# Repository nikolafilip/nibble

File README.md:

# Nibble

A 4-bit computer built from individual transistors, in public.

No integrated circuits anywhere. Transistors, resistors, diodes, capacitors,
LEDs, switches, connectors and wire. Every board is designed in KiCad,
simulated in ngspice, fabricated as a through-hole PCB and hand-soldered.

An AI (Claude) does the schematic generation, simulation and layout.
Nikola sets the constraints, reviews, orders, solders and measures.
The commit trailers say which is which.

## Layout

| Path | What |
|---|---|
| `docs/` | Architecture, instruction set, bus header, gate cell, build plan, decision ledger, known issues |
| `boards/00-origin-calculator/` | The hand-made 3-bit add/subtract calculator this started from, untouched |
| `boards/01-alu/` | 4-bit ALU: add, subtract, and, or, xor, increment, decrement, with flags |
| `boards/02-registers/` | A, B and OUT registers |
| `boards/03-sequencer/` | Step counter, instruction and operand registers, flags, decoders and the diode control matrix |
| `boards/04-program/` | Program memory: 16 words on DIP switches, one page of 256; build more for longer programs |
| `boards/05-clock/` | Clock with a speed knob, RUN/STEP, halt and power-on reset |
| `boards/06-panel/` | Front panel: switches for every line, LEDs on every line, the input port |
| `boards/07-hub/` | Bus hub: power, pull-ups, eight slots |
| `boards/08-memory/` | Data memory: 16 slots of 4 bits, every cell with an LED |
| `boards/09-counter/` | 8-bit program counter and return register |
| `coupon/` | Gate-cell test board: measure the real cell before trusting anything |
| `lib/` | Shared SPICE models and KiCad libraries |
| `sim/` | Generators, testbenches, the emulator and the whole-machine simulation |
| `experiments/muldiv/` | A multiplier/divider designed on the original RTL calculator. Simulated, not built |

## Start here

1. `docs/architecture.md` — what the machine is and how the boards fit together.
2. `docs/isa.md` — the instruction set (31 instructions in 16 opcodes) and a worked program.
3. `docs/bus-header.md` — the 64-pin ribbon header every board shares.
4. `docs/gate-cell.md` — the one logic cell everything is made of.
5. `docs/plan.md` — the gates every board passes before copper exists, and the whole-machine simulation.
6. `docs/cards.md` — the machine as 100 x 100 mm cards on one crimped ribbon (2026-09-10 evening), and the order of work from here.
7. `docs/mounting.md` — the panel it stands on.
8. `docs/DECISIONS.md` — why things are the way they are, in order.

## Status

See `docs/DECISIONS.md` for the latest entry and `docs/KNOWN-ISSUES.md` for what is wrong.

## Licence

CERN-OHL-P-2.0 for the hardware, MIT-equivalent terms for the scripts. See `LICENSE`.

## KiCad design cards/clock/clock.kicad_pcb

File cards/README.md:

# Cards

The machine as 100 x 100 mm boards on one crimped ribbon (docs/cards.md, D042
to D045). Every card has the 64-pin bus header along its top edge, soldered on the
back (D059; pin 1 top left as the front sees the holes, `docs/bus-header.md`),
two M3 holes mid-height on the sides, 100 nF + 10 uF at the top
right, and its logic on the dense tile: 7.68 mm columns, one TO-92 per 5.08
mm row, the pull-up lying along the row above its stack, GND and +5V rails
alternating between the columns on the back. Generated by `sim/build_*_card.py`
from the gate lists in `sim/`; laid out and routed by `sim/pcb.py`. Do not
hand-edit the schematics. Each card's `fab/` folder has the gerbers and their
zip, two renders, the assembly drawing (`<card>-assembly.svg`: which value
goes where, the boards print none) and the parts list. The Nibble logo
(`lib/logo/nibble.png` traced by `sim/logo.py`) is on the sequencer's
front silkscreen alone, one maker's mark on the machine; the cards carry
their name.

| Card | Directory | Transistors | Bus signals | Neighbour link |
|---|---|---|---|---|
| Register bit 0..3 | `reg0` .. `reg3` | 99 each | in: BUS<i>#, CLK, AI, AO, BI, BO, BA, AB, OI. out: A<i>, B<i>. BUS<i># driven open-drain when AO or BO | none |
| ALU bit 0..3 | `alu0` .. `alu3` | 66, 68, 68, 73 | in: A<i>, B<i>, SUB, ONE, F1, F0, EO. out: BUS<i># (open drain); bit 3 also CF, ZF | 2x3: carry C<i+1> and zero-so-far ZS<i> to bit i+1 |
| Counter bit 0..7 | `ctr0` .. `ctr7` | 62 (59 for bit 7) | in: PCL, CLK, RST (bit 0 also PCE). out: PC<i> | 2x3: count carry TC<i+1> to bit i+1; 2x6 chained ribbon from the sequencer: OPR<i>, PCR, RAI |
| Memory control | `memctl` | 57 | in: BUS3..0#, MAI, MI, MO, CLK | 2x6 chained ribbon to the slot cards: MAR3..0 and complements, MIN, MON |
| Memory slot pair | `memslot` (x8) | 91 | BUS3..0# in (MI) and out (MO, open drain) | the ribbon from memory control; jumpers A3 A2 A1 pick the pair |
| Program, four words | `prog` (one per four words) | 41 + 32 diodes | in: PC7..0. out: M7..0 through diodes | none; jumpers P7 P6 P5 P4 G3 G2 pick the addresses 4c..4c+3 |
| Clock | `clock` | 15 + the Schmitt pair | in: HLT. out: CLK, RST | none |
| Hub | `hub` | 0 | every line, on two headers | none |
| Panel A, B, C | `panela`, `panelb`, `panelc` | 28, 20, 32 | A: A3..B0, SUB..AB switched and shown, D3..0 CF ZF CLK RST shown. B: OI..MAI, MI..INP switched and shown, CLK and RST buttons. C: PC7..0, M7..0 shown, DATA switches driven onto BUS# while INP | none |
| Coupon | `coupon` | 57 | power only (a 2-pin header for the bench supply) | none |

## Register bit cards (`reg0` .. `reg3`)

Bit i of the three registers on the bus: A and B (the ALU's operands) and
OUT (the display), as three master-slave D flip-flops with their input muxes
(A takes the bus when AI, B when AB, else holds; B takes the bus when BI, A
when BA, else holds; OUT takes the bus when OI, else holds), the bus driver,
and the card's own two-phase clock (PH1, PH2 from CLK, D033) and hold
decoders. Four designs, the bit baked in, because a bit is three bus lines
and two cards jumpered alike would fight over them. `sim/registers.build_bit`
is the same logic as board 02 sliced per bit; the boards' testbench and the
machine deck take the four cards as the group `regc`.

Verification (2026-09-10), from the kicad-cli exports of the four routed cards
on one bus (`sim/tb_registers.py cards`), the 113-step register script: every
value through A and B, A and B driven back, MOV, XCH, OUT, holds:

| Netlist | Corner | Result |
|---|---|---|
| kicad-cli exports, four cards | TYP, LO, HI | 113 / 113 each |
| kicad-cli exports, four cards | MIX seeds 1, 2, 3 | 113 / 113 each |
| gate list (`cards@dev`) | TYP, LO, HI, MIX 1, 2, 3 | 113 / 113 each |

Machine gate (2026-09-11): `sim/gate.py --boards alu,hub,regc`, all twelve
programs at TYP with the four cards in the deck, 0 mismatches each (fib 127
ticks, calc 616, lfsr 1497, sort 974, mul 314, the rest between).

Layout: each card routes DRC-clean in one freerouting pass (0 unconnected),
ERC clean, 10.3 of 11 tile columns used.

Reproduce from `sim/`:

```
python3 build_reg_card.py 0                    # and 1, 2, 3
<kicad python> pcb.py ../cards/reg0 reg0
python3 tb_registers.py cards out/tb_regcards --corner MIX --seed 2
python3 machine.py programs/fib.asm --boards alu,hub,regc --corner TYP
```

## ALU bit cards (`alu0` .. `alu3`)

Bit i of the ALU: the full adder/subtractor bit (B xor SUB, carry in from
bit i-1), AND, OR, XOR selected by F1 F0, and the open-drain bus driver
while EO. Bit 0 starts the carry with SUB and the zero chain; bit 3 ends
them in CF and ZF on the bus. The carry and zero-so-far run over a 2x3 IDC
link between neighbouring cards (`frame.card_links`: IN at the bottom left,
OUT at the bottom right). `sim/alu.build_bit` is board 01 sliced per bit;
the group `aluc` stands for the four cards in the machine deck.

Verification, from the kicad-cli exports of the four routed cards chained by
their links (`sim/tb_alu.py cards --cases exhaustive`): every A, B, SUB, ONE,
F1 F0 combination, 2304 cases.

| Netlist | Corner | Result |
|---|---|---|
| kicad-cli exports, four cards | TYP | 2304 / 2304, worst settle 54 us |
| kicad-cli exports, four cards | LO | 2304 / 2304, worst settle 28 us |
| kicad-cli exports, four cards | HI | 2304 / 2304, worst settle 90 us |
| kicad-cli exports, four cards | MIX seed 1 | 2304 / 2304, worst settle 69 us |
| gate list (`cards@dev`) | TYP | 2304 / 2304 |

Layout: alu0 and alu3 route in one freerouting pass; alu1 and alu2 needed
the 300-pass cap and the 0.6 mm via (their last net drops from the bus
header into the first column). All four DRC clean, 0 unconnected.

## Counter bit cards (`ctr0` .. `ctr7`)

Bit i of the program counter (count when PCE, load the jump target OPR<i>
when PCL, load the return address RA<i> when PCR, clear on RST) and of the
return register RA (a transparent latch open while RAI and PH1). The count
carry TC<i+1> = TC<i> and PC<i> runs over the 2x3 links; the sequencer's
operand and load lines come down a chained 2x6 ribbon (`frame.card_ribbon`),
each card taking its own OPR line. Group `ctrc`.

Verification: `call.asm` on the eight cards from the gate lists, 0
mismatches; the exports carry every program of the step 9 gate
(`sim/results/gate25_*.md`).

## Memory control and slot cards (`memctl`, `memslot`)

Control: the four-bit address register MAR (transparent latches open while
MAI and MPH) and the write and read gates MIN (low while MI and MPH) and
MON (low while MO), sent to the slot cards over a chained 2x6 ribbon with
MAR and its complements. MPH is a pulse in the middle of the tick (D054):
CLKD is CLK through 100k into 2.2 nF on the sheet, and MPH = NOR(CLK, NOT
CLKD) is high from the falling edge of CLK until CLKD decays past a
threshold, 60 to 350 us, so the address latch closes and the write ends
hundreds of microseconds before the next rising edge. The first card gated
both with PH1, the low half of CLK, which ends at the rising edge: with the
clock card's 35 us edge and the threshold spread between cards, the
sequencer stepped and the next tick's data reached the bus 10 us before this
card saw the edge, and the address latch took the data as the address (gcd,
list and logic at mixed seed 2 wrote slots 12, 9 and 15 instead of 0). Slot pair:
two 4-bit slots (even: MAR0 = 0, odd: MAR0 = 1) of the pair the three
jumpers select (A3 A2 A1: the centre pin to '1' where the address bit is 1),
eight cross-coupled cells with their write and read pull-downs, and an LED
per cell. One design, eight cards, jumpered 0 to 7. Group `memc`.

The jumpers bring MAR1..3 (or their complements) onto the card, so in the
deck they are ports of the slot subcircuit (`machine.ports_of`); left
inside they float, and every read came from slot pair 7.

Verification, `sim/tb_memory.py cards`: three fills of all sixteen slots
and reads back, single writes between reads, bus noise while nothing loads,
217 steps. `--race` is the edge as the memory card saw it in the machine:
CLK rises over 35 us, the bus switches 10 us into the rise and the control
lines 100 us after it (they lag every edge by 60 to 170 us).

| Netlist | Corner | Result |
|---|---|---|
| PH1-gated card (before D054), gate list, `--race` | TYP, HI, MIX 1, MIX 2 | 121, 121, 121, 170 / 217 (`sim/out/tb_memory_oldD054_race.log`) |
| PH1-gated card (before D054), gate list, `--race` | LO | 217 / 217 (the card sees the edge at 0.8 V, before the bus moves) |
| D054 card, gate list (`dev`) | TYP, LO, HI, MIX 1..4 | 217 / 217 each (`sim/out/tbmem54_dev.log`, `tbmem54_mix.log`) |
| D054 card, gate list (`dev`), `--race` | TYP, LO, HI, MIX 1..4 | 217 / 217 each |
| D054 card, kicad-cli exports, control + eight slot cards | TYP; `--race` TYP, LO, HI, MIX 1, MIX 2 | 217 / 217 each (`sim/out/tbmem54_cards.log`) |

Layout: both cards route DRC clean in one pass, 0 unconnected.

## Program card (`prog`)

Four words of eight DIP switches; a closed switch pulls its M line high
through a diode while the word's row is selected (3.3k row pull-ups, so a
row of eight ones still reads 3.8 V against the hub's 220k, D048). Six 1x3 jumpers strap the
card to its addresses: P7..P4 the page (PC7..4), G3 G2 the word group
(PC3..2), the centre pin to '1' where the address bit is 1; PC1..0 pick the
word. A program of n words takes ceil(n/4) cards (`list` 6, `sort` 20). In
the deck (`progc`) one copy per four words is instantiated with its jumpers
and switches set from the assembled program; `prog.map.json` says which
diode is word w bit i.

Verification: `fib.asm` on the card gate lists with the ALU and hub, 0
mismatches; the exports carry every program of the step 9 gate
(`sim/results/gate25_*.md`).

## Clock card (`clock`)

Board 05's circuit on a card: the source-coupled Schmitt RC oscillator with
the speed pot and SLOW jumper, the RUN/STEP switch, the halt gate, the
power-on reset, and the hold-off (`sim/clock.py`, drawn by
`build_clock_card.py`). The hold-off (D064): a 2N7000 from the oscillator's
timing node X to ground through 100 ohm, its gate on the RST line. While
RST is high the timing capacitor is held empty, the Schmitt trigger reads
low and the clock gate holds CLK low; when RST lets go, the card's own
reset or the panel's button, X charges from 0 V and the first clock edge
comes 1.3 to 5.7 ms later at the fastest setting (`sim/results/reset_release.md`,
`starts_hold.md`), never in the 45 us in which the cards leave their
resets, which had started the machine wrong once in a hundred times
(`sweep_por.md`). HLT
reaches the halt gate through 100k into 2.2 nF (0.22 ms, D050), so the
clock pulse that started the halt step completes before the clock stops.
CLK's pull-up in RUN is 1k and RST comes from a 1k inverter stage (RD = NOT
PB) through 100 ohm and a diode, against the panel's 10k pull-downs (D053):
into the machine's 3 nF CLK rises 0.5 to 3.5 V in about 6 us (the first card
took 35 to 43 us, and the cards, each reading the edge with its own
transistors, saw it up to 25 us apart) and RST releases in 45 us (the first
card's drifted for 8 ms and more, so cards left reset on different edges).
`sim/tb_clock.py` measures both under that load and requires them
(TYP, LO, HI, MIX 1..2 pass: `sim/out/tb_clock_cards54_*.log`; the first
card under the same bench: CLK rise 43 us, RST never released cleanly,
`sim/out/tb_clock_cards_oldD053_TYP.log`).
Deck name `clkc`. The step 9 gate runs with this card driving CLK and RST
and no testbench clock or reset, every deck a power-up from 0 V: all
thirteen programs at TYP and the 24 corners, 0 mismatches
(`sim/results/gate25_TYP.md`, `gate25_corners.md`). The first card, in the
same deck, passed all thirteen at TYP and lost gcd, list and logic at MIX
seed 2 to the address-latch race its slow edge opened
(`sim/results/gate_clk_corners_oldclock.md`, D053, D054).

## Hub card (`hub`)

Two bus headers, one along the top edge and one along the bottom, one per
column face's ribbon (D043), the 64 lines routed between them. Ground is
wired, not poured: a ring above the top header's pads, down the right edge
and below the bottom header's, with bars for the capacitors, the LED and
the M pull-downs (the lines cut a pour to islands). The bench supply's
banana leads into two 4 mm sockets standing on the front face (Cal Test
CT3151V1, soldered in on four pins, D063), 19.05 mm apart so a dual plug
fits (no USB, D057), through a 1.5 A polyfuse (D052) and past a crowbar
(D061: above 6.3 to 7.8 V a zener fires an SCR that holds the rail near
1 V; a 3 A diode takes crossed leads; `sim/results/crowbar.md`), the four bus pull-ups, the eight M-line pull-downs (220k, D048:
with 1 Meg an M line released by a jump took 0.6 ms to fall), a power LED,
100 uF, test loops on BUS3..0, CLK and RST, and an empty spot (C-RST,
do not populate) for a 2.2 nF from RST to ground should the scope show
more pickup on RST than the simulation says (bring-up section 9). Deck
name `hubc`.

## Panel cards (`panela`, `panelb`, `panelc`)

A: DIP-8 level switches for A3..A0 B3..B0 and SUB EO AI AO BI BO BA AB
(10k to +5V: a switch left on never fights a card pulling low), LEDs for
those lines, for the bus data (an inverter per BUS<i>#), CF, ZF, CLK and
RST. B: switches and LEDs for OI IO II PCE PCL FI HLT MAI and MI MO WRL
WRH ONE F0 F1 INP, and the CLK and RST buttons with their RC debounce and
Schmitt triggers (the second inverter has a 1k pull-up and drives the line
through 100 ohm and a diode, D053). C, the operator's card: PC7..0 and M7..0
LEDs, the four DATA switches and the input port (driven onto BUS# while
INP). Every switched or observed line has a 1Meg pull-down on the tile
(`PD` cells) except M, pulled down on the hub, and CLK and RST, whose
pull-downs on card A are 10k (D053: they set the falling edges of both
lines, 30 us into 3 nF). The LEDs read row by row like the old
panel: a tile column holds one panel column (three LEDs on A, two on B and
C). Group `pnl`.

## Coupon card (`coupon`)

Every cell in copper, each with a test loop, powered from a 2-pin header
on the bench supply or from the bus header (D056, `sim/coupon.py`,
`sim/build_coupon_card.py`): the 5-inverter ring (a buffered loop and a raw
one on the ring node), fan-out 1 and 10, 3-input NAND and NOR, a bus driver
with the hub-style 10k pull-up, the clock card's oscillator (the Schmitt
pair and its 100k + 47 nF, drawn on the sheet as on `clock`), a master-slave
flip-flop wired as a toggle with its asynchronous reset (RST on the input
header), the D053 line driver (1k inverter, 100 ohm, diode, 10k pull-down;
the bench clips 3.3 nF on its loop), a diode-connected transistor on 4.7k
that reads its own threshold, a program row (3.3k, 1N4148, 220k), an LED.
Inputs IN, N1..N3, RST on a 1x6 header with 1 Meg pull-downs (PD tiles);
fifteen loops including GND and +5V. 57 transistors on six tile columns,
routed in one freerouting pass, DRC clean.

`sim/tb_coupon.py kicad` simulates the routed card's export at TYP, LO, HI
and MIX seeds 1..3 with a x10 probe on every loop and writes the bands
the bench must land in: `sim/results/coupon_expected.md` (ring 5.9 to
23.6 us, fan-out-10 rise 67 to 77 us, oscillator 1.64 to 2.55 ms, Q at
half that, DRV rise 6.6 us and fall 49 us into 3.3 nF, VTO 0.88 to 3.02 V,
5 to 14 mA). `dev` runs the gate list plus the sheet-drawn parts and gives
the same numbers at the uniform corners, so the sheet matches the design.
Two things the testbench found that the bench should know: with
low-threshold transistors the ring swings only to about 2 V and a
high-threshold buffer never switches (hence the raw RING0 loop), and while
RST holds the flip-flop a pulse of up to 4 V and 10 us can appear on Q at a
rising clock edge at some threshold mixes (the master's release racing the
slave's copy; the machine's masters are closed then, and every MIX run of
the machine gate passed with it). Its own testbench sheet is excluded from
the board.

Reproduce from `sim/`:

```
python3 build_coupon_card.py
<kicad python> pcb.py ../cards/coupon coupon
python3 tb_coupon.py kicad out/tb_coupon --all
```

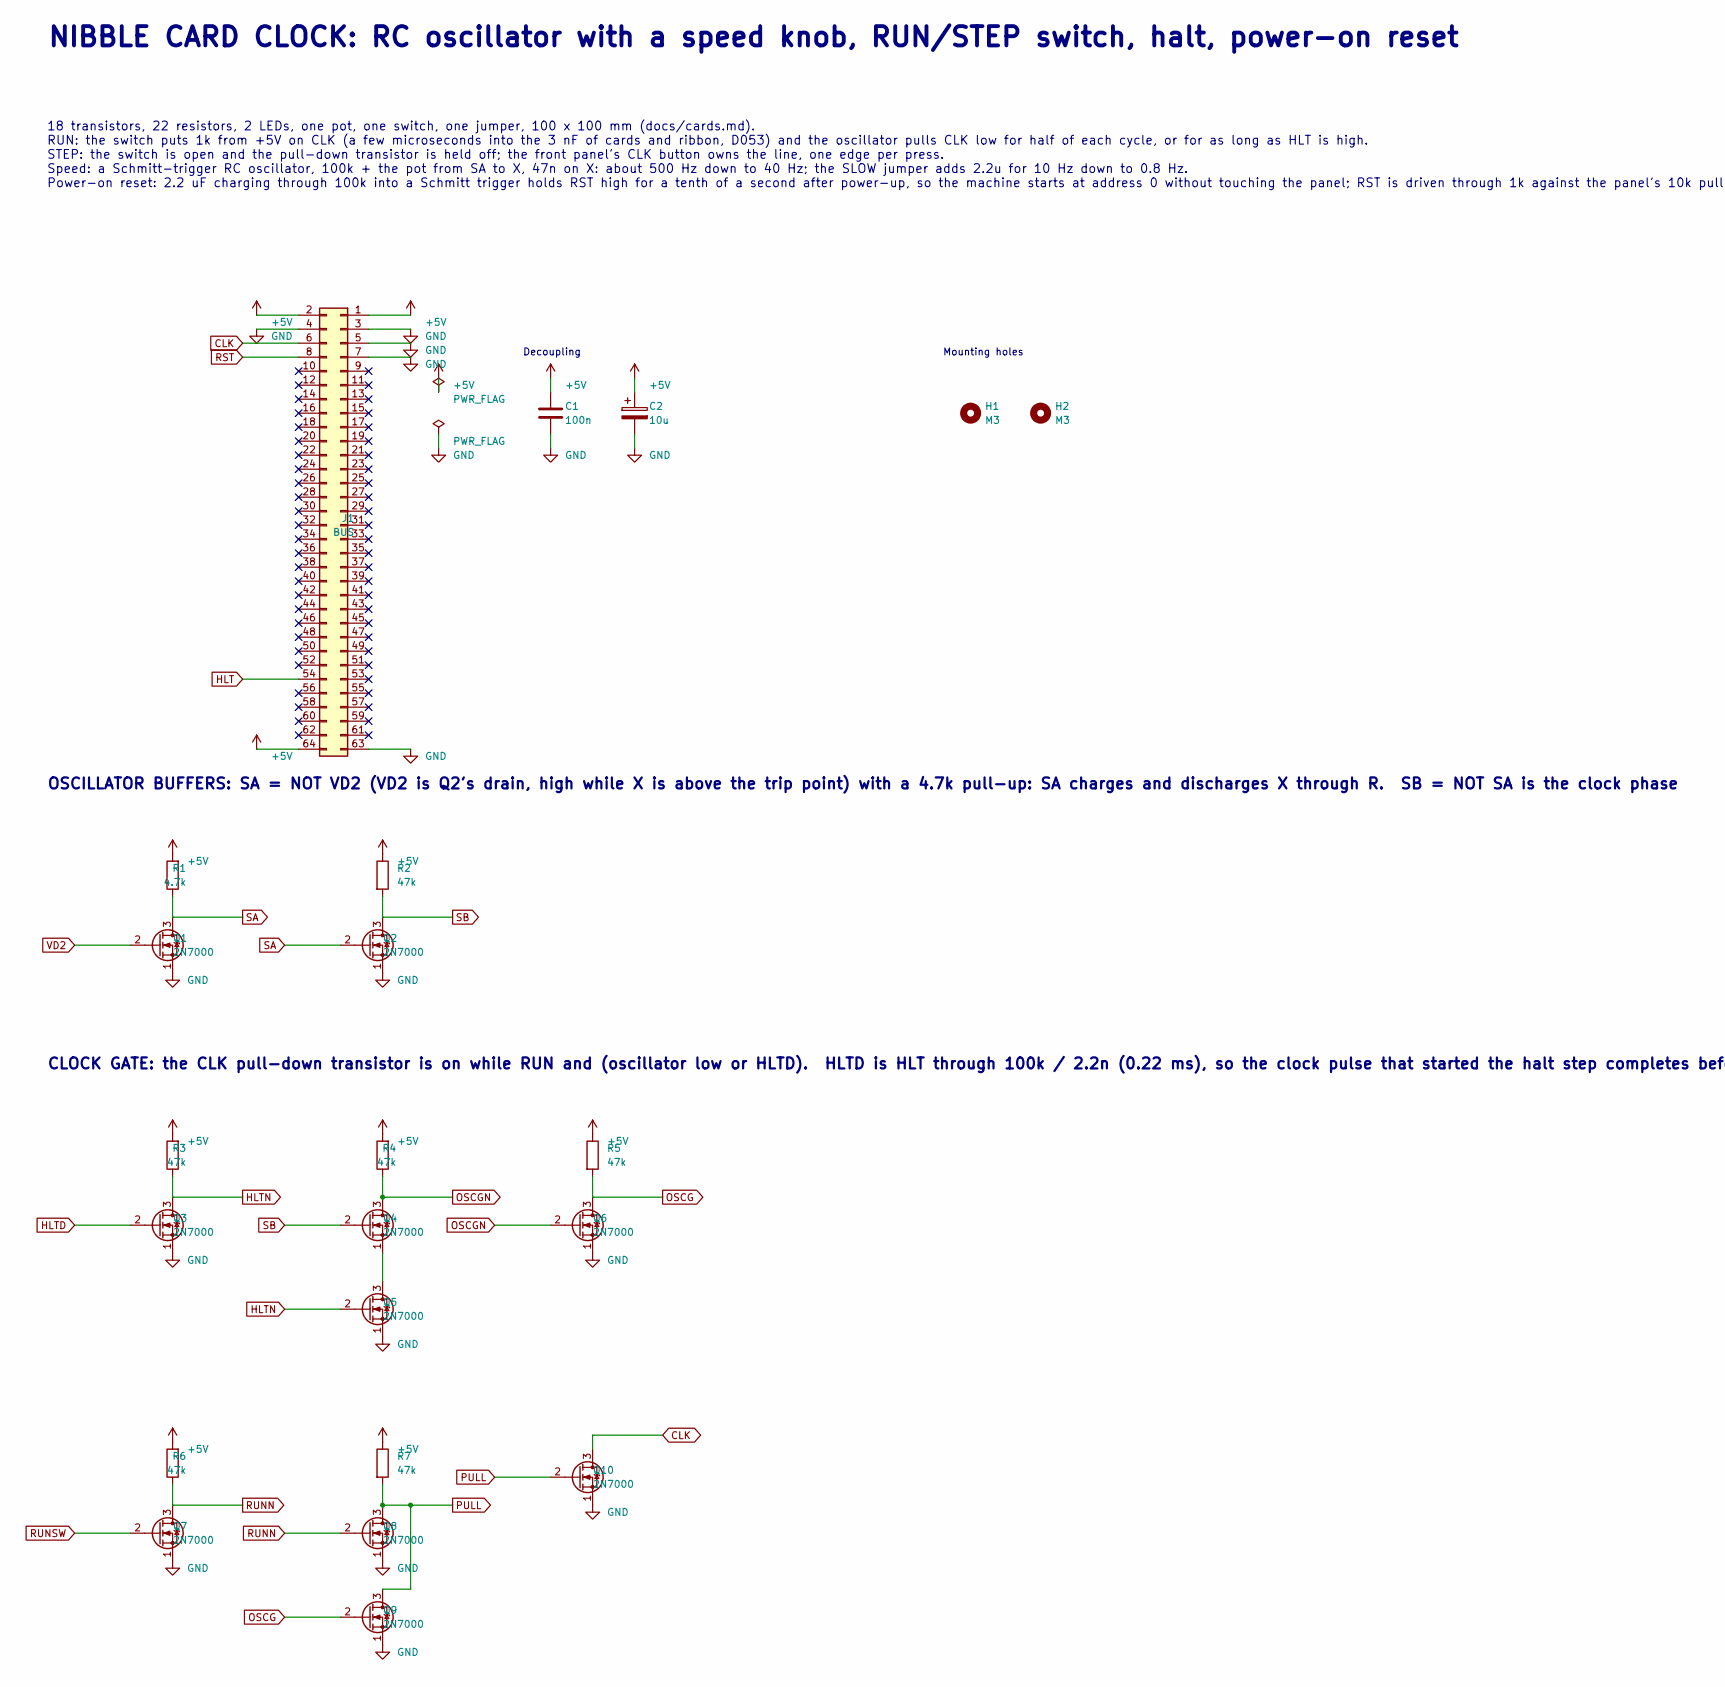
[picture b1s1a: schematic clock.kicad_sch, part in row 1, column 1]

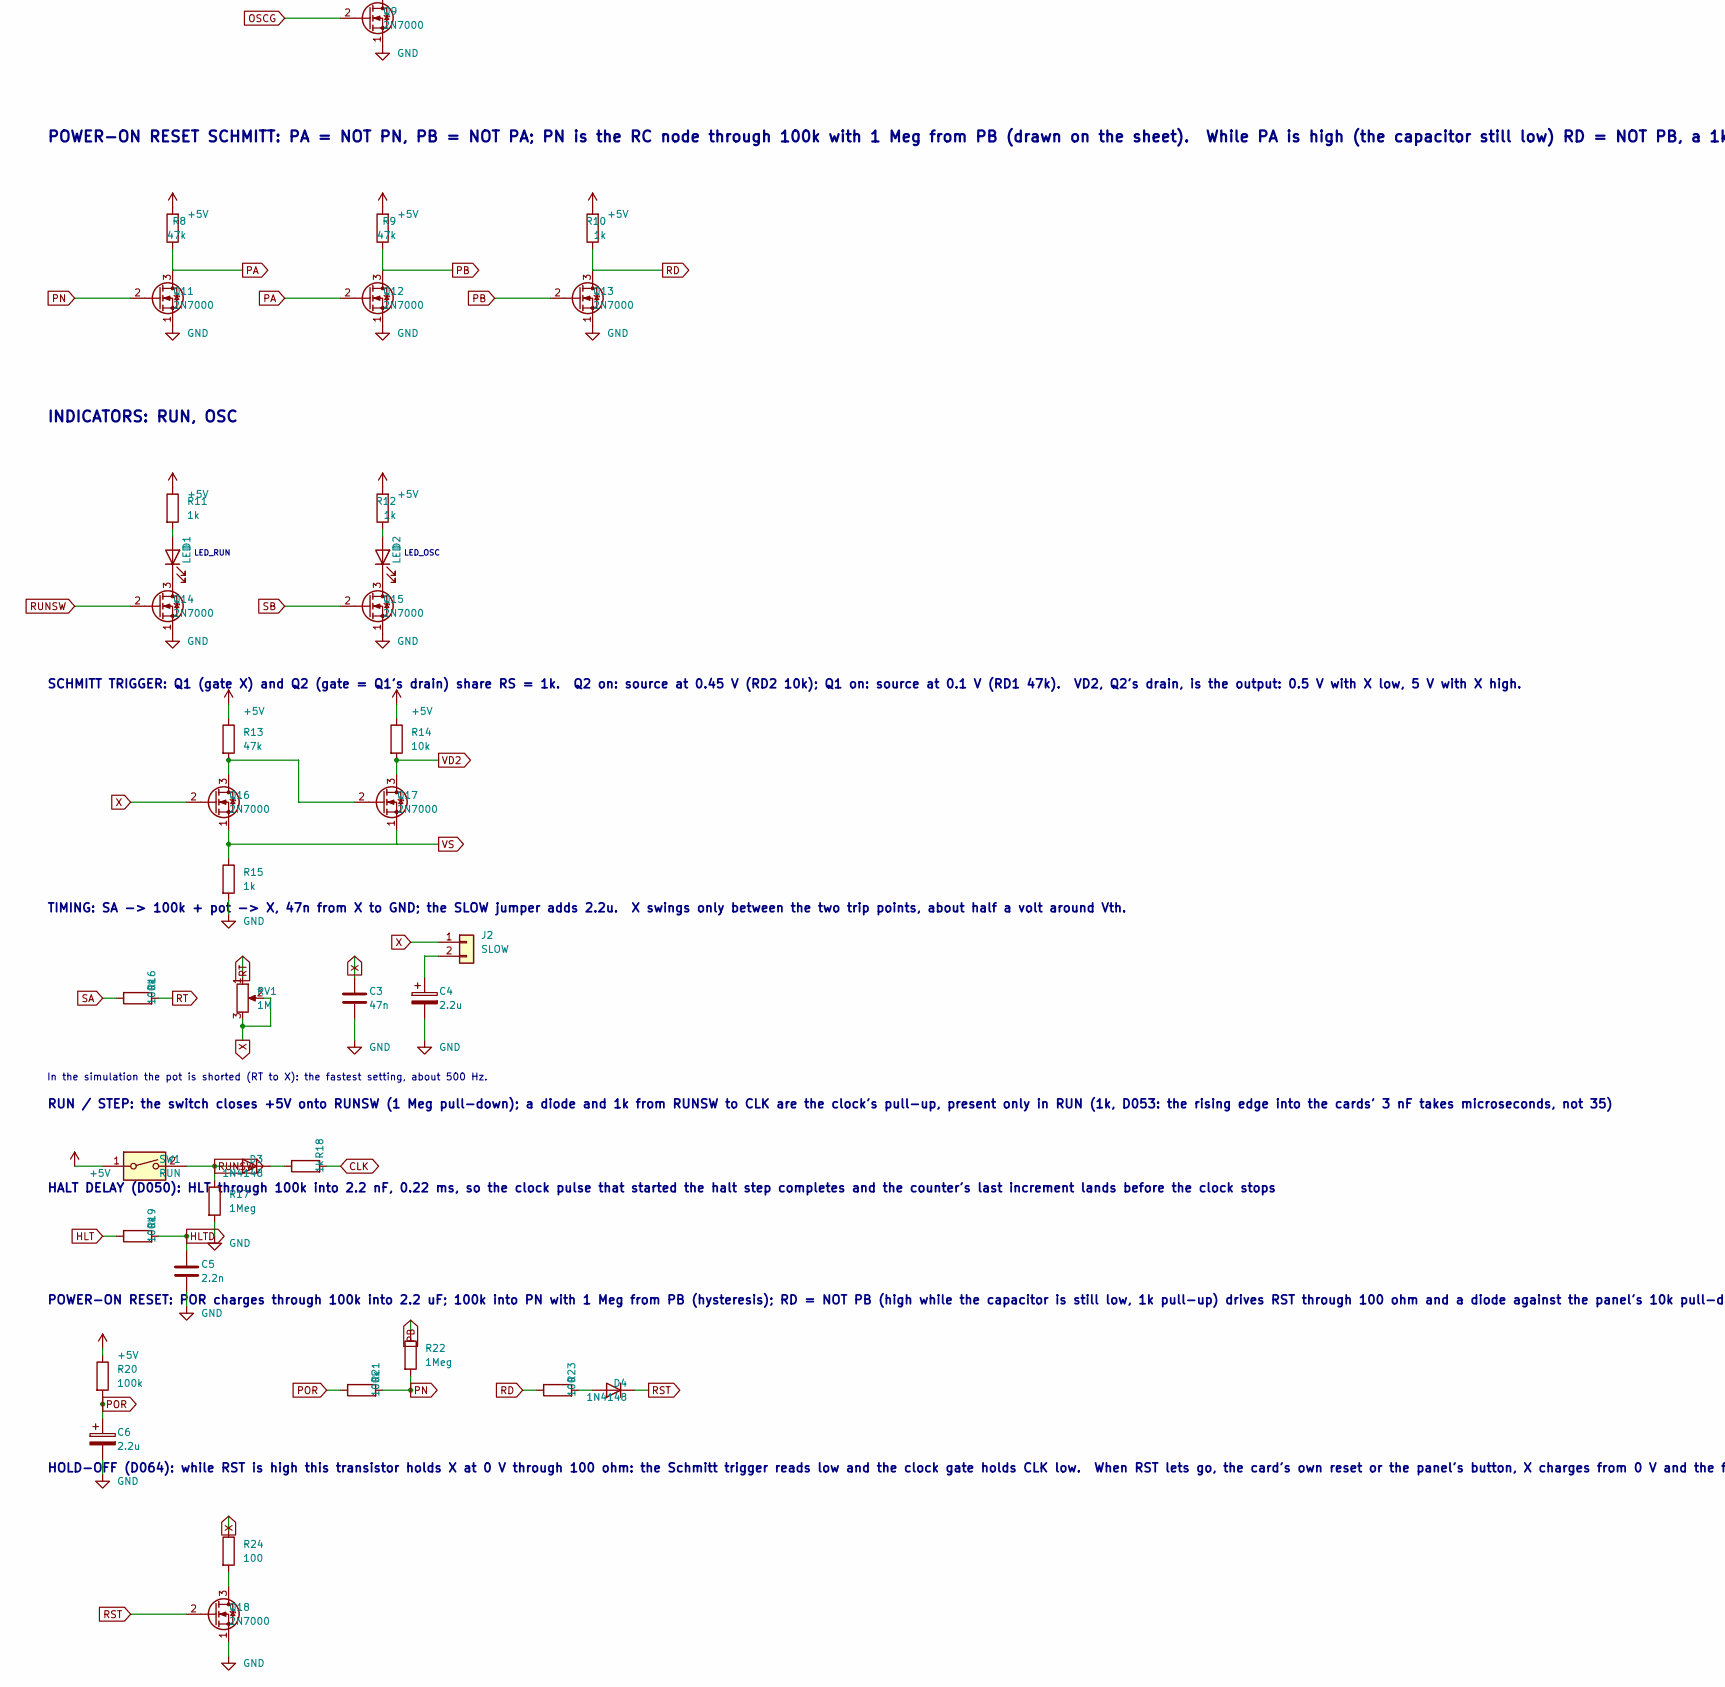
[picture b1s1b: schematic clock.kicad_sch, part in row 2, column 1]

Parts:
C1: 100n; C_Disc_D5.0mm_W2.5mm_P2.50mm
C2: 10u; CP_Radial_D5.0mm_P2.00mm
C3: 47n; C_Disc_D5.0mm_W2.5mm_P2.50mm
C4, C6: 2.2u; CP_Radial_D5.0mm_P2.00mm
C5: 2.2n; C_Disc_D5.0mm_W2.5mm_P2.50mm
D1, D2: LED; LED_D3.0mm
D3, D4: 1N4148; D_DO-35_SOD27_P7.62mm_Horizontal
H1, H2: M3; MountingHole_3.2mm_M3_Pad
J1: BUS; IDC-Header_2x32_P2.54mm_Vertical
J2: SLOW; PinHeader_1x02_P2.54mm_Vertical
Q1, Q2, Q3, Q4, Q5, Q6, Q7, Q8, Q9, Q10, Q11, Q12, Q13, Q14, Q15, Q16, Q17, Q18: 2N7000; TO-92_Inline_Wide
R1: 4.7k; R_Axial_DIN0207_L6.3mm_D2.5mm_P5.08mm_Vertical
R2, R3, R4, R5, R6, R7, R8, R9, R13: 47k; R_Axial_DIN0207_L6.3mm_D2.5mm_P5.08mm_Vertical
R10, R11, R12, R15, R18: 1k; R_Axial_DIN0207_L6.3mm_D2.5mm_P5.08mm_Vertical
R14: 10k; R_Axial_DIN0207_L6.3mm_D2.5mm_P5.08mm_Vertical
R16, R19, R20, R21: 100k; R_Axial_DIN0207_L6.3mm_D2.5mm_P5.08mm_Vertical
R17, R22: 1Meg; R_Axial_DIN0207_L6.3mm_D2.5mm_P5.08mm_Vertical
R23, R24: 100; R_Axial_DIN0207_L6.3mm_D2.5mm_P5.08mm_Vertical
RV1: 1M; Potentiometer_Bourns_PTV09A-4_Single_Vertical
SW1: RUN; SW_DIP_SPSTx01_Slide_9.78x4.72mm_W7.62mm_P2.54mm

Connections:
+5V: C1.1, C2.1, J1.1, J1.2, J1.64, R1.2, R2.1, R3.2, R4.2, R5.1, R6.2, R7.1, R8.2, R9.2, R10.2, R11.1, R12.2, R13.1, R14.1, R20.1, SW1.1
CLK: J1.6, Q10.3 (D), R18.2
GND: C1.2, C2.2, C3.2, C4.2, C5.2, C6.2, J1.3, J1.4, J1.5, J1.7, J1.63, Q1.1 (S), Q2.1 (S), Q3.1 (S), Q5.1 (S), Q6.1 (S), Q7.1 (S), Q8.1 (S), Q9.1 (S), Q10.1 (S), Q11.1 (S), Q12.1 (S), Q13.1 (S), Q14.1 (S), Q15.1 (S), Q18.1 (S), R15.2, R17.2
HLT: J1.54, R19.1
HLTD: C5.1, Q3.2 (G), R19.2
HLTN: Q3.3 (D), Q5.2 (G), R3.1
unnamed: D1.2 (A), R11.2
unnamed: D1.1 (K), Q14.3 (D)
unnamed: D2.2 (A), R12.1
unnamed: D2.1 (K), Q15.3 (D)
unnamed: D3.1 (K), R18.1
unnamed: D4.2 (A), R23.2
unnamed: C4.1, J2.2
unnamed: Q4.1 (S), Q5.3 (D)
unnamed: Q16.3 (D), Q17.2 (G), R13.2
unnamed: Q18.3 (D), R24.2
OSCG: Q6.3 (D), Q9.2 (G), R5.2
OSCGN: Q4.3 (D), Q6.2 (G), R4.1
PA: Q11.3 (D), Q12.2 (G), R8.1
PB: Q12.3 (D), Q13.2 (G), R9.1, R22.1
PN: Q11.2 (G), R21.2, R22.2
POR: C6.1, R20.2, R21.1
PULL: Q8.3 (D), Q9.3 (D), Q10.2 (G), R7.2
RD: Q13.3 (D), R10.1, R23.1
RST: D4.1 (K), J1.8, Q18.2 (G)
RT: R16.2, RV1.1
RUNN: Q7.3 (D), Q8.2 (G), R6.1
RUNSW: D3.2 (A), Q7.2 (G), Q14.2 (G), R17.1, SW1.2
SA: Q1.3 (D), Q2.2 (G), R1.1, R16.1
SB: Q2.3 (D), Q4.2 (G), Q15.2 (G), R2.2
VD2: Q1.2 (G), Q17.3 (D), R14.2
VS: Q16.1 (S), Q17.1 (S), R15.1
X: C3.1, J2.1, Q16.2 (G), R24.1, RV1.2, RV1.3

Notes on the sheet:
NIBBLE CARD CLOCK: RC oscillator with a speed knob, RUN/STEP switch, halt, power-on reset
18 transistors, 22 resistors, 2 LEDs, one pot, one switch, one jumper, 100 x 100 mm (docs/cards.md). RUN: the switch puts 1k from +5V on CLK (a few microseconds into the 3 nF of cards and ribbon, D053) and the oscillator pulls CLK low for half of each cycle, or for as long as HLT is high. STEP: the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
OSCILLATOR BUFFERS: SA = NOT VD2 (VD2 is Q2's drain, high while X is above the trip point) with a 4.7k pull-up: SA charges and discharges X through R. SB = NOT SA is the clock phase
CLOCK GATE: the CLK pull-down transistor is on while RUN and (oscillator low or HLTD). HLTD is HLT through 100k / 2.2n (0.22 ms), so the clock pulse that started the halt step completes before the clock stops (D050)
POWER-ON RESET SCHMITT: PA = NOT PN, PB = NOT PA; PN is the RC node through 100k with 1 Meg from PB (drawn on the sheet). While PA is high (the capacitor still low) RD = NOT PB, a 1k pull-up, drives RST through 100 ohm and a diode; the panel's 10k pull-down releases it in tens of microseconds (D053)
INDICATORS: RUN, OSC
LED_RUN
LED_OSC
Decoupling
Mounting holes
SCHMITT TRIGGER: Q1 (gate X) and Q2 (gate = Q1's drain) share RS = 1k. Q2 on: source at 0.45 V (RD2 10k); Q1 on: source at 0.1 V (RD1 47k). VD2, Q2's drain, is the output: 0.5 V with X low, 5 V with X high.
TIMING: SA -> 100k + pot -> X, 47n from X to GND; the SLOW jumper adds 2.2u. X swings only between the two trip points, about half a volt around Vth.
In the simulation the pot is shorted (RT to X): the fastest setting, about 500 Hz.
RUN / STEP: the switch closes +5V onto RUNSW (1 Meg pull-down); a diode and 1k from RUNSW to CLK are the clock's pull-up, present only in RUN (1k, D053: the rising edge into the cards' 3 nF takes microseconds, not 35)
HALT DELAY (D050): HLT through 100k into 2.2 nF, 0.22 ms, so the clock pulse that started the halt step completes and the counter's last increment lands before the clock stops
POWER-ON RESET: POR charges through 100k into 2.2 uF; 100k into PN with 1 Meg from PB (hysteresis); RD = NOT PB (high while the capacitor is still low, 1k pull-up) drives RST through 100 ohm and a diode against the panel's 10k pull-down (D053)
HOLD-OFF (D064): while RST is high this transistor holds X at 0 V through 100 ohm: the Schmitt trigger reads low and the clock gate holds CLK low. When RST lets go, the card's own reset or the panel's button, X charges from 0 V and the first clock edge comes 1.3 to 5.4 ms later at the fastest setti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

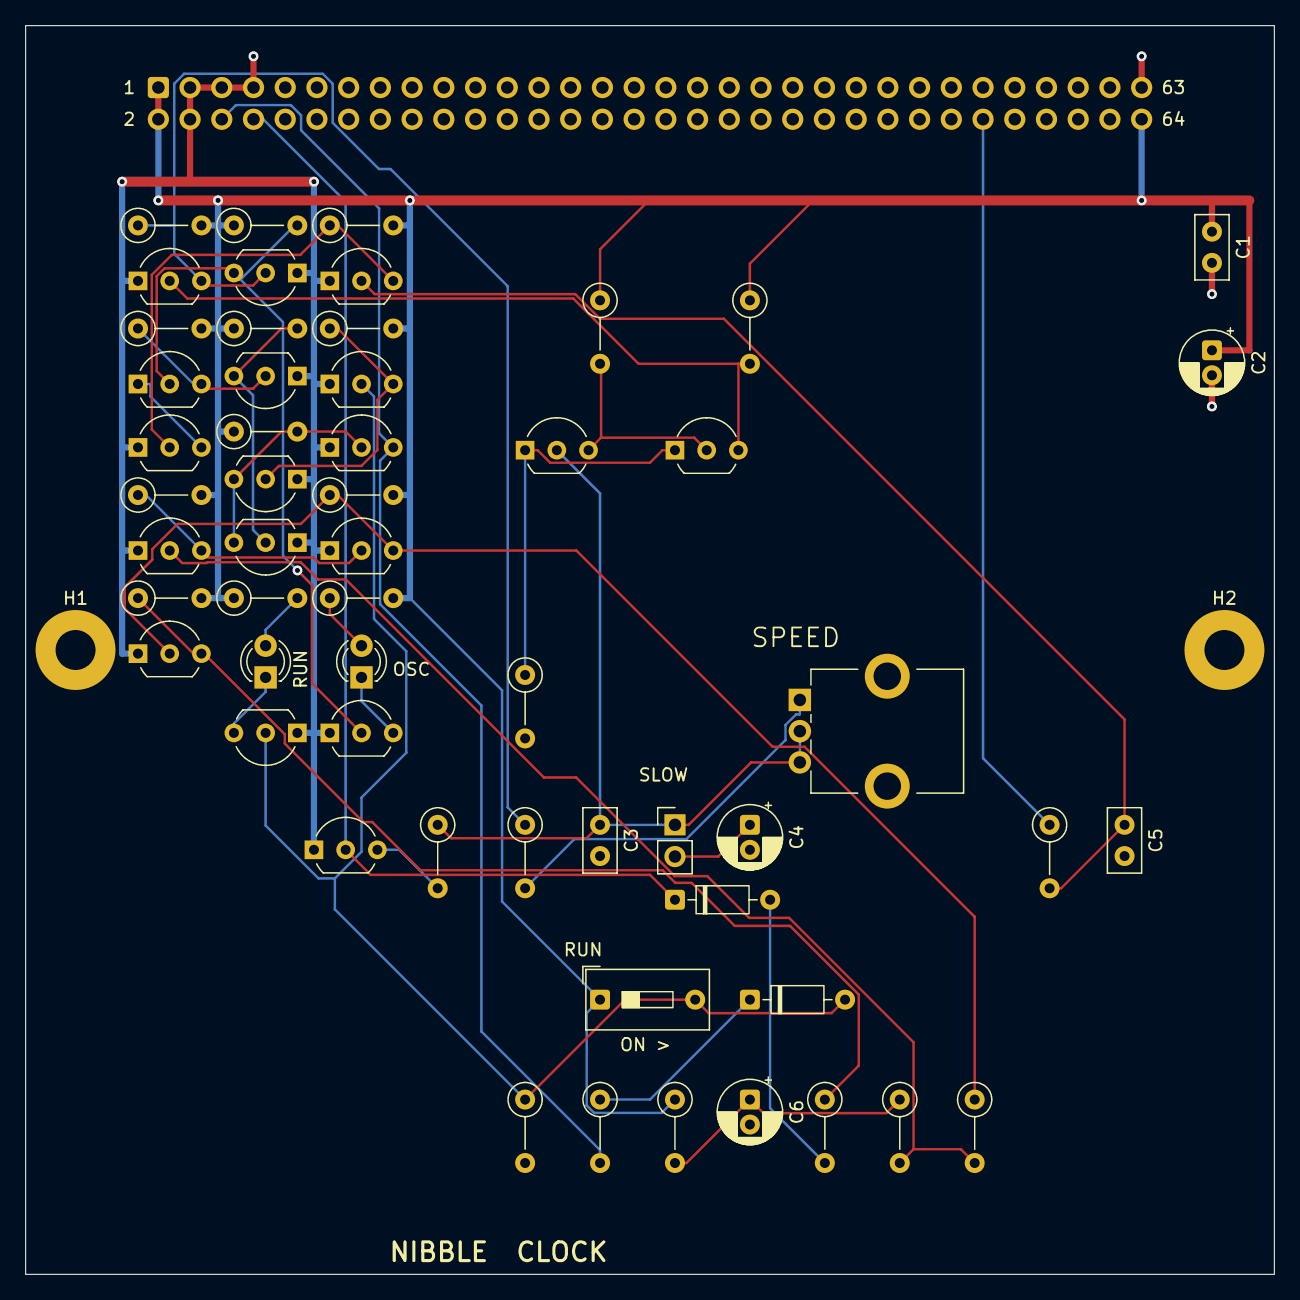
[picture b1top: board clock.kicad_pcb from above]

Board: 2 copper layers, 100.0 x 100.0 mm, 58 parts (1 on the bottom side), 33 nets.

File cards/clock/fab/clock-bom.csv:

"Reference","Value","Footprint","QUANTITY"
"C1","100n","Capacitor_THT:C_Disc_D5.0mm_W2.5mm_P2.50mm","1"
"C2","10u","Capacitor_THT:CP_Radial_D5.0mm_P2.00mm","1"
"C3","47n","Capacitor_THT:C_Disc_D5.0mm_W2.5mm_P2.50mm","1"
"C4,C6","2.2u","Capacitor_THT:CP_Radial_D5.0mm_P2.00mm","2"
"C5","2.2n","Capacitor_THT:C_Disc_D5.0mm_W2.5mm_P2.50mm","1"
"D1,D2","LED","LED_THT:LED_D3.0mm","2"
"D3,D4","1N4148","Diode_THT:D_DO-35_SOD27_P7.62mm_Horizontal","2"
"J1","BUS","Connector_IDC:IDC-Header_2x32_P2.54mm_Vertical","1"
"J2","SLOW","Connector_PinHeader_2.54mm:PinHeader_1x02_P2.54mm_Vertical","1"
"Q1-Q18","2N7000","Package_TO_SOT_THT:TO-92_Inline_Wide","18"
"R1","4.7k","Resistor_THT:R_Axial_DIN0207_L6.3mm_D2.5mm_P5.08mm_Vertical","1"
"R2-R9,R13","47k","Resistor_THT:R_Axial_DIN0207_L6.3mm_D2.5mm_P5.08mm_Vertical","9"
"R10-R12,R15,R18","1k","Resistor_THT:R_Axial_DIN0207_L6.3mm_D2.5mm_P5.08mm_Vertical","5"
"R14","10k","Resistor_THT:R_Axial_DIN0207_L6.3mm_D2.5mm_P5.08mm_Vertical","1"
"R16,R19-R21","100k","Resistor_THT:R_Axial_DIN0207_L6.3mm_D2.5mm_P5.08mm_Vertical","4"
"R17,R22","1Meg","Resistor_THT:R_Axial_DIN0207_L6.3mm_D2.5mm_P5.08mm_Vertical","2"
"R23,R24","100","Resistor_THT:R_Axial_DIN0207_L6.3mm_D2.5mm_P5.08mm_Vertical","2"
"RV1","1M","nibble:Potentiometer_Bourns_PTV09A-4_Single_Vertical","1"
"SW1","RUN","Button_Switch_THT:SW_DIP_SPSTx01_Slide_9.78x4.72mm_W7.62mm_P2.54mm","1"
